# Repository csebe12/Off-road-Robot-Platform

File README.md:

# Off-road-Robot-Platform
This repository contains the instructions and code to set up an off-road tracked platform using DFRobot's Yuewalker chassis.

This is how the assembled robot will look like:

The webserver was developed to be mobile friendly. The following pictures show how the UI looks like on desktop (top view) and on a mobile device (bottom view).

## Control panel

The first panel is the control panel. On the top, the green circle indicates that the UART communication between the Raspberry Pi and Pyboard works properly. If there is an error, it will turn red. The live camera feed is displayed on the left. The robot can be controlled by the blue joystick on the right. The output from the joystick is transformed into left and right motor values using the arcade mixing function. The different power settings enable precise and fast movements. On the bottom, the servos can be setup on the go. Once the user clicks setup, the servo can be plugged in into the corresponding port and it can be controlled using the two arrows. Servos can be deinitialized by clicking the off button.

## Navigation panel

The second panel is used for setting up and monitoring the autonomous mode. The map is displayed using the Leaflet JavaScript library. The map tiles were downloaded using the RgoogleMaps package and are stored on the Raspberry Pi. This enables the users to use the map without internet connection. Waypoints can either be added by entering their latitude and longitude or simply by clicking on the map. The waypoint can then be added to the list by clicking insert. Any waypoint can be removed from or added to the list, or can be set as home. Waypoints are uploaded to the Pyboard by clicking the upload button. Data such as the battery voltage, the motor’s current consumption and navigation information are displayed on the right. When the navigation is started the bottom four buttons will have the same colours as the LEDs.

## Command history

The third panel shows the command history. To distinguish between the Pyboard’s and the Rasperry Pi’s messages, those sent by the Raspberry Pi have a blue background. The most popular actions can be called by clicking the buttons, or the user can issue any command by entering it to the input box.

# Setup
## Hardware
The robot uses two MCUs, a Pyboard v1.1 and a Raspberry Pi Zero W. The latter can be exchanged to any WiFi enabled Raspberry Pi.
The schematic, layout and bill of materials to assemble the control unit can be found in the control-unit folder.
## Pyboard
The application requires threads and double precision floating points. To achieve this, the firmware needs to be updated from [the official website](https://micropython.org/download/pybv1/).
The code is located in the micropython folder. Without precompilation, its size too big to store on the Pyboard's flash, so an SD card is required.
### SD card booting
The SD card cannot be directly mounted on startup, because the buck converter cannot handle the sudden current surge. To fix this, put the pybrestart.py file on the flash. This will do a hard reset after 3 seconds. Then the SD card will be mounted.
### Files
Upload all the files from the micropython folder to the Pyboard's SD card except for the pybrestart.py
## Raspberry Pi
### [Enable I2C and SSH](https://itsfoss.com/ssh-into-raspberry/)
### Install Flask
```
sudo pip install flask + pip install -U flask-cors
```
Here are some useful flask tutorials:
* https://learn.sparkfun.com/tutorials/using-flask-to-send-data-to-a-raspberry-pi/all
* https://www.instructables.com/id/Smooth-Web-Browser-Motor-Control/
* https://pythonhow.com/add-css-to-flask-website/

### Access point
Follow [this tutorial](https://www.raspberryconnect.com/projects/65-raspberrypi-hotspot-accesspoints/168-raspberry-pi-hotspot-access-point-dhcpcd-method).
If you get at any point a "Temporary failure in name resolution" error you can fix it by running
```
sudo sh –c ‘echo “nameserver 8.8.8.8” >> /etc/resolv.conf’
```
### Files
Upload the files from the rpi folder. The script is started by running thread.py. To run it, use the following command:
```
sudo -E -H python3 thread.py
```
### Starting script on boot
Use the rc.local method with the commmand above following [this tutorial](https://www.dexterindustries.com/howto/run-a-program-on-your-raspberry-pi-at-startup/)
### Reverting to WiFi
By running wifi-access.sh you can revert back to using WiFi. Conversely, by running access-point.sh the Raspberry Pi will act as an access point. You must restart before the changes take place.
### Offline map tiles
You can save Google Maps tiles from your desired area using [this tutorial](http://rgooglemaps.r-forge.r-project.org/OfflineMaps-RgoogleMaps-leaflets.html). Once you downloaded the map tiles, save it on the Raspberry Pi in the app/static/mapTiles folder.
# Operation
Here is an overview of the components:

Below is the system's block diagram

## Commands
To see the full list of complete commands, examine the cmd.py file in the micropython/lib directory.

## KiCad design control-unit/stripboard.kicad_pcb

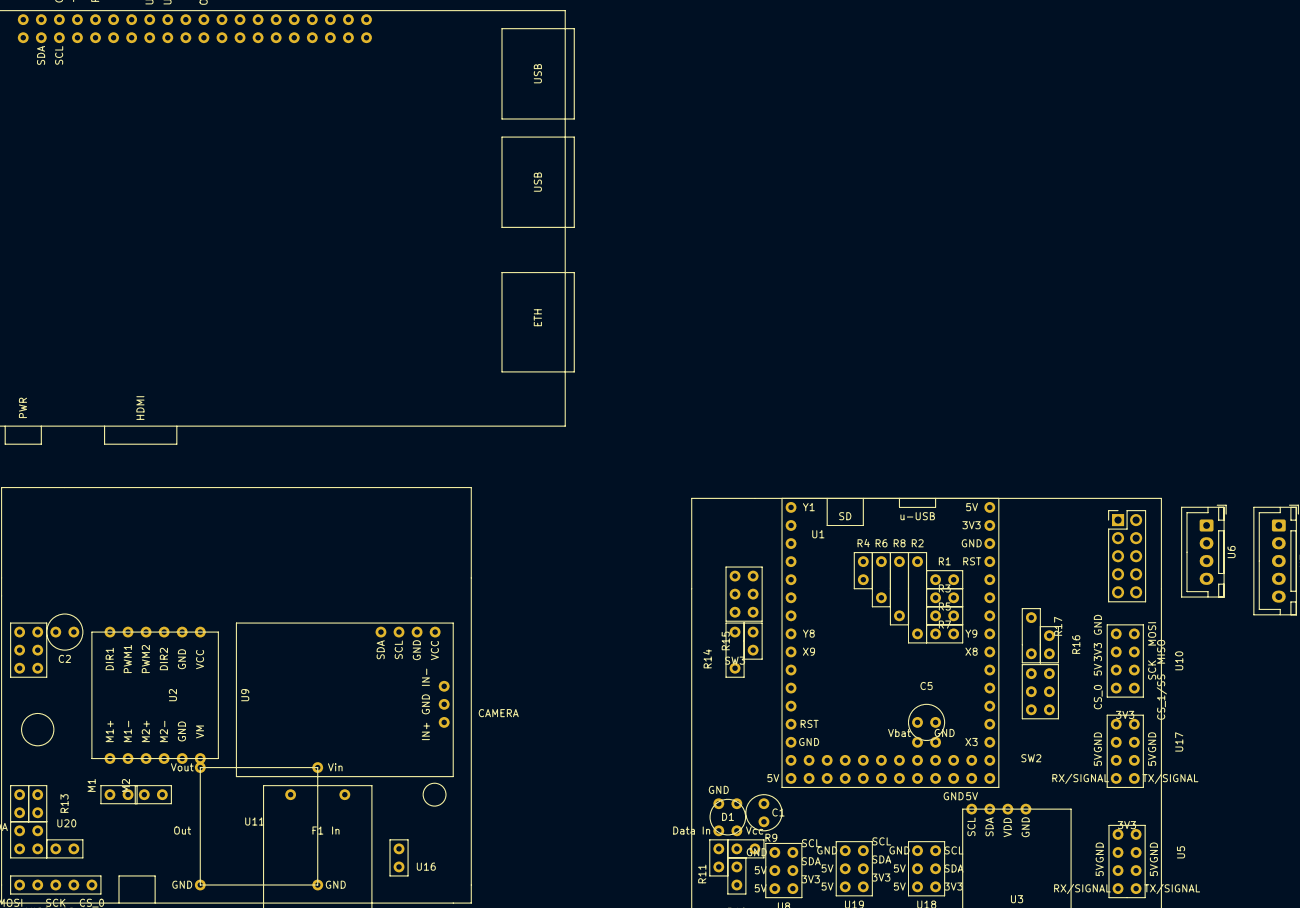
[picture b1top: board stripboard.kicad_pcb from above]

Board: 2 copper layers, 46 parts (0 on the bottom side), 55 nets, no tracks yet.

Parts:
C1: 0.1 uF; capacitor
C2, C5: 100 nF; capacitor
D1: NeoPixel_THT; Neopixel
F1: Fuse; fuse
JST: Battery voltage; PinHeader_2x05_P2.54mm_Vertical
M1, M2: Motor_DC; screw-terminal
R1, R3, R5, R7: 1k; R
R2, R4, R6, R8: 1.8k; R
R9: 1.6k; R
R10: 560; R
R11: 470; R
R12, R13, R14, R15, R16, R17: 10k; R
SW1, SW2, SW3: SW_Push_DPDT; dpdt
U1: Pyboard
U2: TB6612
U3: MPU-9250
U4: RaspberryPi3-Z; Raspberry Pi 3 Model B
U5, U17: servo-uart
U6: JST-XH-4; JST_XH_B4B-XH-A_1x04_P2.50mm_Vertical
U7: JST-XH-5; JST_XH_B5B-XH-A_1x05_P2.50mm_Vertical
U8, U18, U19: i2c-v1
U9: INA219
U10: spi
U11: buck-converter; buck converter
U12: spi-RPi
U15: i2c-Rpi; i2c Rpi
U16: power; screw-terminal
U20: uart

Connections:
3V3: SW1.2, SW1.5, SW2.2, SW2.5, SW3.2, SW3.5, U3.2, U4.1, U5.1, U8.6, U9.1, U10.5, U17.1, U17.5, U18.6, U19.6
5V: C2.1, C5.1, R10.1, U1.1, U2.6, U4.4, U5.3, U8.3, U8.5, U10.3, U11.3, U17.3, U17.7, U18.3, U18.5, U19.3, U19.5
GND: C1.1, C2.2, D1.2, R2.1, R4.1, R6.1, R8.1, R9.2, U2.5, U2.11, U3.1, U4.6, U5.2, U6.1, U7.1, U8.1, U9.2, U9.6, U10.7, U11.4, U17.2, U17.6, U18.1, U19.1
unnamed: C1.2, D1.3, R9.1, R10.2
unnamed: C5.2, U1.2
unnamed: D1.4, R11.2
unnamed: F1.2, U16.1
unnamed: M1.1, U2.7
unnamed: M1.2, U2.8
unnamed: M2.1, U2.9
unnamed: M2.2, U2.10
unnamed: R1.1, U6.2, U7.2
unnamed: R1.2, R4.2, U1.Y12
unnamed: R2.2, R7.2, U1.X11
unnamed: R3.1, U6.3, U7.3
unnamed: R3.2, R6.2, U1.Y11
unnamed: R5.1, U6.4, U7.4
unnamed: R5.2, R8.2, U1.X12
unnamed: R7.1, U7.5
unnamed: R11.1, U1.Y7
unnamed: R12.1, U4.3, U15.1
unnamed: R12.2, SW1.1
unnamed: R13.1, U4.5, U15.2
unnamed: R13.2, SW1.4
unnamed: R14.1, U1.X10, U8.4
unnamed: R14.2, SW3.1
unnamed: R15.1, U1.X9, U8.2
unnamed: R15.2, SW3.4
unnamed: R16.1, U1.Y9, U3.4, U9.3, U18.2, U19.2
unnamed: R16.2, SW2.1
unnamed: R17.1, U1.Y10, U3.3, U9.4, U18.4, U19.4
unnamed: R17.2, SW2.4
unnamed: U1.X1, U5.4
unnamed: U1.X2, U5.8
unnamed: U1.X3, U17.4
unnamed: U1.X4, U17.8
unnamed: U1.X5, U10.2
unnamed: U1.X6, U10.4
unnamed: U1.X7, U10.6
unnamed: U1.X8, U10.8
unnamed: U1.Y3, U2.2
unnamed: U1.Y4, U2.3
unnamed: U1.Y5, U2.1
unnamed: U1.Y6, U2.4
unnamed: U2.12, U9.5
unnamed: U11.2, U16.2
unnamed: U4.19, U12.1
unnamed: U4.21, U12.2
unnamed: U4.23, U12.3
unnamed: U4.26, U12.4
unnamed: U4.24, U12.5
unnamed: U4.16, U20.1
unnamed: U4.18, U20.2
RPi(RX)-Pyb(TX): U1.Y2, U4.8
RPi(TX)-Pyb(RX): U1.Y1, U4.10

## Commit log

2020-05-03 Repository folder update
2020-05-03 Documentation updated
2020-05-03 Readme update
2020-05-08 Bug fixes for autonomous mode
2020-09-15 README updated
